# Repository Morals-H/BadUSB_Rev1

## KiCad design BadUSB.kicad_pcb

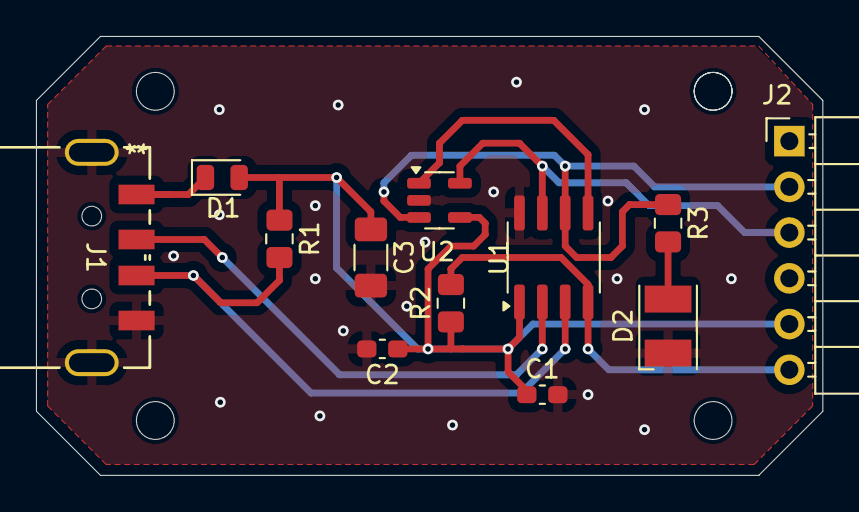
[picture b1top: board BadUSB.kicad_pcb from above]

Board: 2 copper layers, 43.7 x 24.4 mm, 12 parts (0 on the bottom side), 9 nets.

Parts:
C1, C2: 0.1uF; C_0603_1608Metric_Pad1.08x0.95mm_HandSolder
C3: 10uF; C_1206_3216Metric_Pad1.33x1.80mm_HandSolder
D1: D_Schottky; D_0805_2012Metric
D2: LED; LED_PLCC-2_3.4x3.0mm_KA
J1: USB_A; USBA_2.0_Male
J2: Conn_01x06_Pin; PinHeader_1x06_P2.54mm_Horizontal
R1: 1.5k; C_0805_2012Metric_Pad1.18x1.45mm_HandSolder
R2: 10m; C_0805_2012Metric_Pad1.18x1.45mm_HandSolder
R3: 330; C_0805_2012Metric_Pad1.18x1.45mm_HandSolder
U1: PIC12F1840-xSN; SOIC-8_3.9x4.9mm_P1.27mm
U2: 24AA02-OT; SOT-23-5

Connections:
D+: J1.3 (D+), R1.2, U1.3 (RA4)
D-: J1.2 (D-), U1.2 (RA5)
GND: C1.2, C2.2, C3.2, D2.1 (K), J1.4 (GND), J1.7, J1.8, J2.3, U1.8 (VSS), U2.2 (V_{SS})
MCLR: J2.1, R2.2, U1.4 (RA3)
unnamed: D2.2 (A), R3.2
PGC: J2.5, R3.1, U1.6 (RA1), U2.3 (SDA)
PGD: J2.4, U1.7 (RA0), U2.5 (WP)
SCL: U1.5 (RA2), U2.1 (SCL)
VDD: C1.1, C2.1, C3.1, D1.1 (K), D1.2 (A), J1.1 (VBUS), J2.2, R1.1, R2.1, U1.1 (VDD), U2.4 (V_{CC})

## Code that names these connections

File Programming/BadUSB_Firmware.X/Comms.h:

#ifndef COMMS_H
#define COMMS_H
#define _XTAL_FREQ 8000000  // 8 MHz clock for delay calculation

// Pin definitions for USB communication
#define WP RA0   // Set high to lock
#define SDA RA1  // Serial data
#define SCL RA2  // Serial clock
#define MCLR RA3 // Ignore
#define DPLUS RA4  // D+ (RA4)
#define DMINUS RA5 // D- (RA5)

// Main function prototypes
void send_keystroke(void);
void write_rom(void);
void read_rom(void);
void write_ram(uint8_t* data, uint8_t start_addr);
void read_ram(uint8_t start, uint8_t range);
void check_ram(void);
void clear_ram(void);

// I2C function prototypes
void i2c_delay(void);            // I2C delay function for proper timing
void i2c_start(void);            // Generate I2C Start condition
void i2c_stop(void);
void i2c_send_byte(uint8_t data); // Send one byte of data via I2C
uint8_t i2c_receive_byte(void);  // Receive one byte of data via I2C
void i2c_wp_start(void);         // Declare i2c_wp_start function
void i2c_wp_stop(void);         // Declare i2c_wp_stop function
void eeprom_write(uint8_t mem_addr, uint8_t data);
void eeprom_write_string(uint8_t start_addr, const char* str);          // Generate I2C Stop condition

// USB function prototypes
void delay_us(uint16_t us);            // USB delay function in microseconds
void usb_send_bit(uint8_t bit);        // Send one bit of data via USB
void usb_send_byte(uint8_t data);      // Send one byte of data via USB
void usb_send_report(uint8_t *report); // Send a USB HID report

// Function prototypes for keycode and RAM functions
uint8_t get_keycode(char key);  // Declare get_keycode function

// External declarations for global variables
extern const uint8_t keycodes[]; // Declare keycodes as an external array

#endif // COMMS_H

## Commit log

2025-03-28 Initial
2025-03-29 cleaned up traces and fix silkscreen
2025-03-30 code initial state
